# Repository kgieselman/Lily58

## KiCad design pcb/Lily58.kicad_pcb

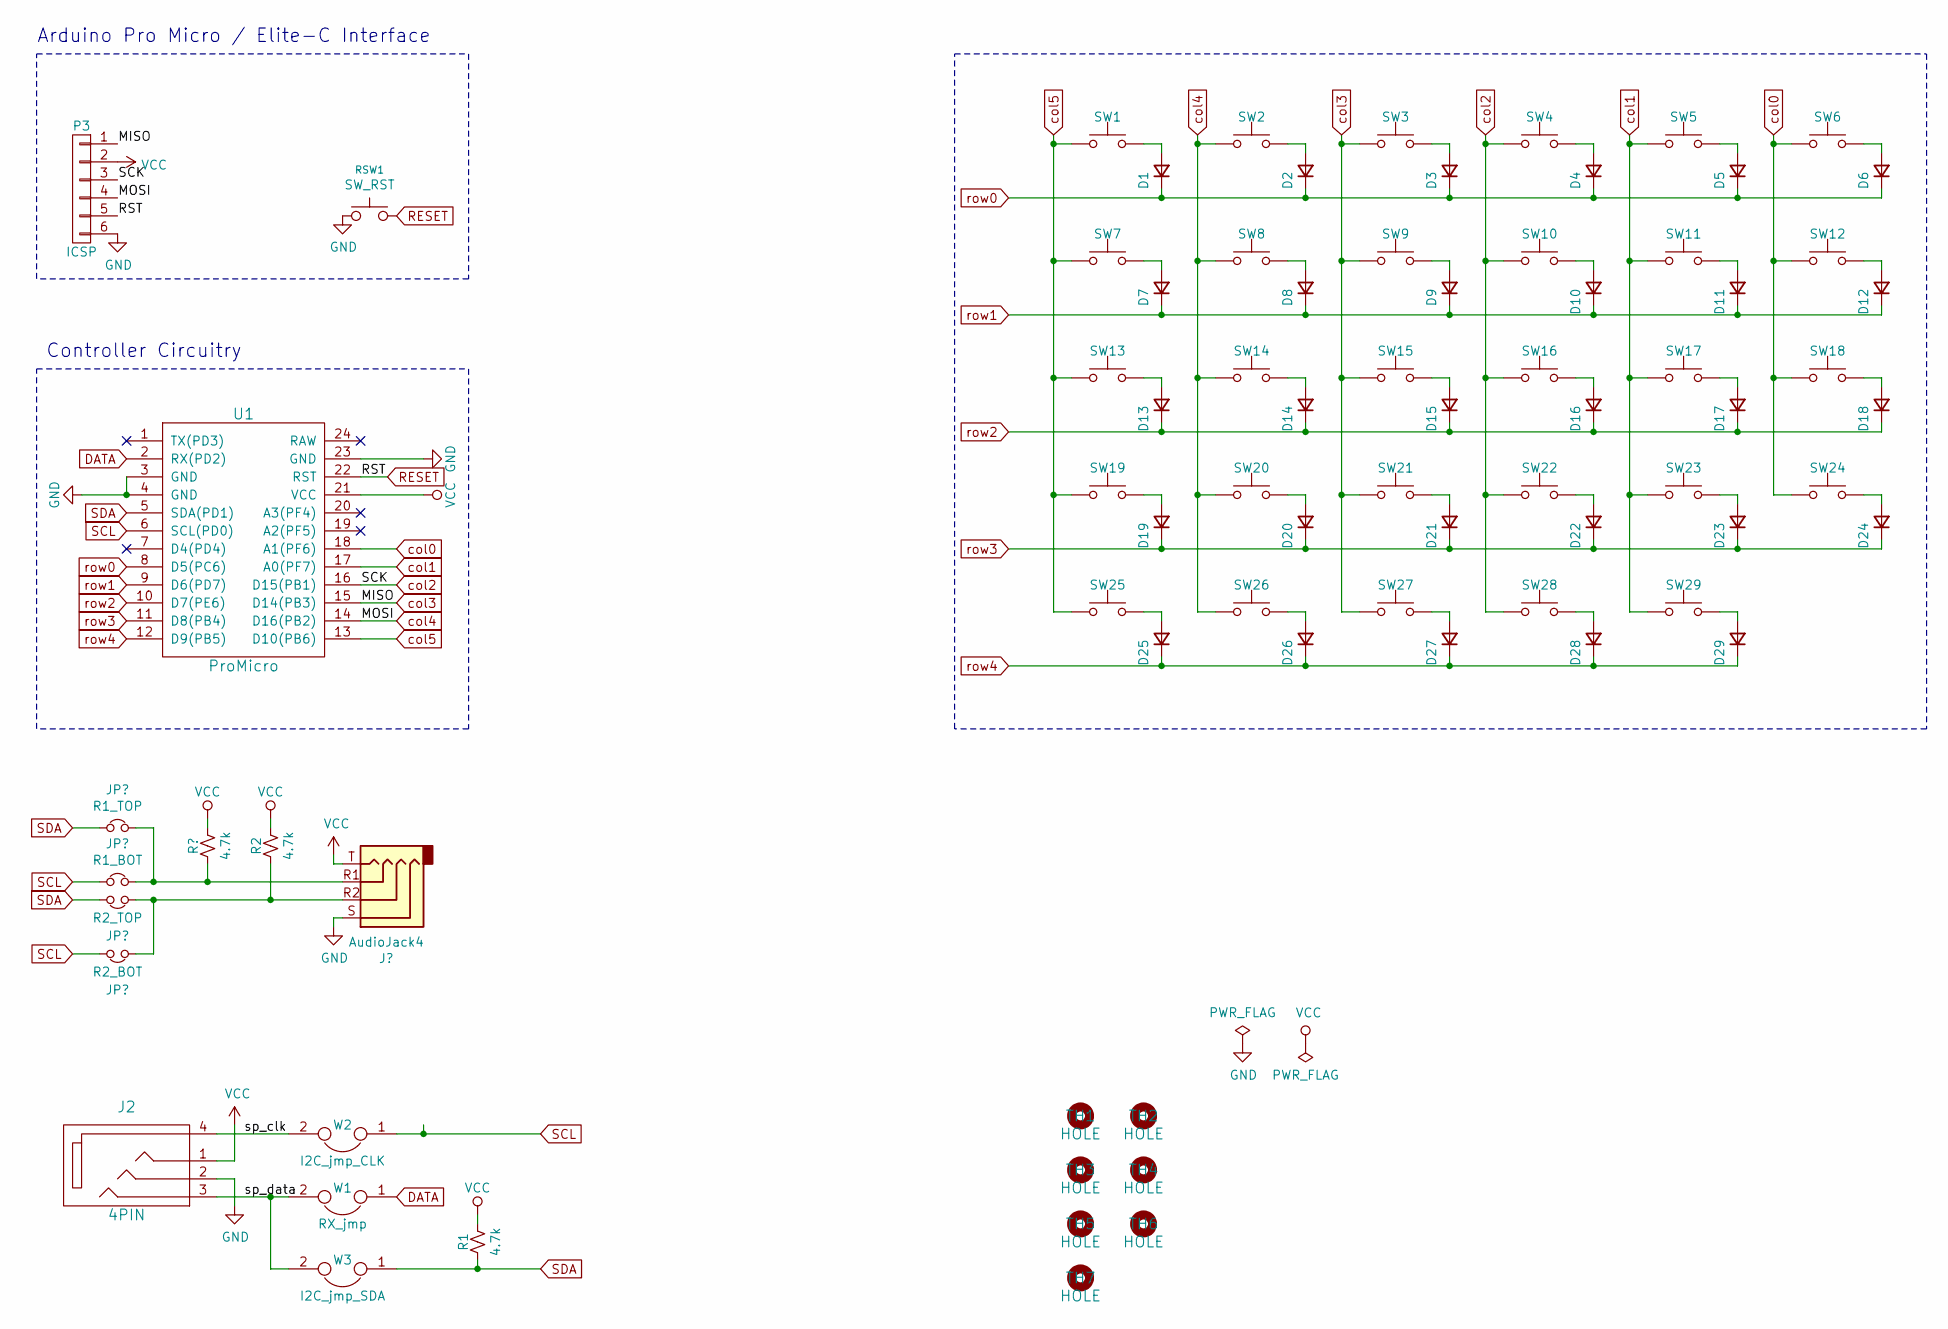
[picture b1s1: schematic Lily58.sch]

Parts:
D1, D2, D3, D4, D5, D6, D7, D8, D9, D10, D11, D12, D13, D14, D15, D16, D17, D18, D19, D20, D21, D22, D23, D24, D25, D26, D27, D28, D29: D; D_SOD-123
J2: 4PIN; MJ-4PP-9
P3: ICSP
R1, R2: 4.7k; R_0603
RSW1: SW_RST; TACT_SWITCH_TVBP06
SW1, SW2, SW3, SW4, SW5, SW6, SW7, SW8, SW9, SW10, SW11, SW12, SW13, SW14, SW15, SW16, SW17, SW18, SW19, SW20, SW21, SW22, SW23, SW24, SW25, SW27, SW28, SW29: SW_PUSH; MX_1U
SW26: SW_PUSH; MX_PG1350-Under_FLIP_HOLES_27mm
TH1, TH2: HOLE; HOLE_M2
TH3, TH4, TH5, TH6, TH7: HOLE; HOLE_M2_TH
U1: ProMicro; ProMicro_rev
W1: RX_jmp; jumper_data
W2: I2C_jmp_CLK; jumper_data
W3: I2C_jmp_SDA; jumper_data

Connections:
/sp_clk: J2.4, W2.2
/sp_data: J2.3, W1.2, W3.2
DATA: U1.2 (RX(PD2)), W1.1
GND: J2.2, P3.6, RSW1.1, U1.3 (GND), U1.4 (GND), U1.23 (GND)
unnamed: D1.2 (A), SW1.2
unnamed: D2.2 (A), SW2.2
unnamed: D3.2 (A), SW3.2
unnamed: D4.2 (A), SW4.2
unnamed: D5.2 (A), SW5.2
unnamed: D6.2 (A), SW6.2
unnamed: D7.2 (A), SW7.2
unnamed: D8.2 (A), SW8.2
unnamed: D9.2 (A), SW9.2
unnamed: D10.2 (A), SW10.2
unnamed: D11.2 (A), SW11.2
unnamed: D12.2 (A), SW12.2
unnamed: D13.2 (A), SW13.2
unnamed: D14.2 (A), SW14.2
unnamed: D15.2 (A), SW15.2
unnamed: D16.2 (A), SW16.2
unnamed: D17.2 (A), SW17.2
unnamed: D18.2 (A), SW18.2
unnamed: D19.2 (A), SW19.2
unnamed: D20.2 (A), SW20.2
unnamed: D21.2 (A), SW21.2
unnamed: D22.2 (A), SW22.2
unnamed: D23.2 (A), SW23.2
unnamed: D24.2 (A), SW24.2
unnamed: D25.2 (A), SW25.2
unnamed: D26.2 (A), SW26.2
unnamed: D27.2 (A), SW27.2
unnamed: D28.2 (A), SW28.2
unnamed: D29.2 (A), SW29.2
RESET: P3.5, RSW1.2, U1.22 (RST)
SCL: R2.2, U1.6 (SCL(PD0)), W2.1
SDA: R1.2, U1.5 (SDA(PD1)), W3.1
VCC: J2.1, P3.2, R1.1, R2.1, U1.21 (VCC)
col0: SW6.1, SW12.1, SW18.1, SW24.1, U1.18 (A1(PF6))
col1: SW5.1, SW11.1, SW17.1, SW23.1, SW29.1, U1.17 (A0(PF7))
col2: P3.3, SW4.1, SW10.1, SW16.1, SW22.1, SW28.1, U1.16 (D15(PB1))
col3: P3.1, SW3.1, SW9.1, SW15.1, SW21.1, SW27.1, U1.15 (D14(PB3))
col4: P3.4, SW2.1, SW8.1, SW14.1, SW20.1, SW26.1, U1.14 (D16(PB2))
col5: SW1.1, SW7.1, SW13.1, SW19.1, SW25.1, U1.13 (D10(PB6))
row0: D1.1 (K), D2.1 (K), D3.1 (K), D4.1 (K), D5.1 (K), D6.1 (K), U1.8 (D5(PC6))
row1: D7.1 (K), D8.1 (K), D9.1 (K), D10.1 (K), D11.1 (K), D12.1 (K), U1.9 (D6(PD7))
row2: D13.1 (K), D14.1 (K), D15.1 (K), D16.1 (K), D17.1 (K), D18.1 (K), U1.10 (D7(PE6))
row3: D19.1 (K), D20.1 (K), D21.1 (K), D22.1 (K), D23.1 (K), D24.1 (K), U1.11 (D8(PB4))
row4: D25.1 (K), D26.1 (K), D27.1 (K), D28.1 (K), D29.1 (K), U1.12 (D9(PB5))

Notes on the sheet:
Arduino Pro Micro / Elite-C Interface
Controller Circuitry

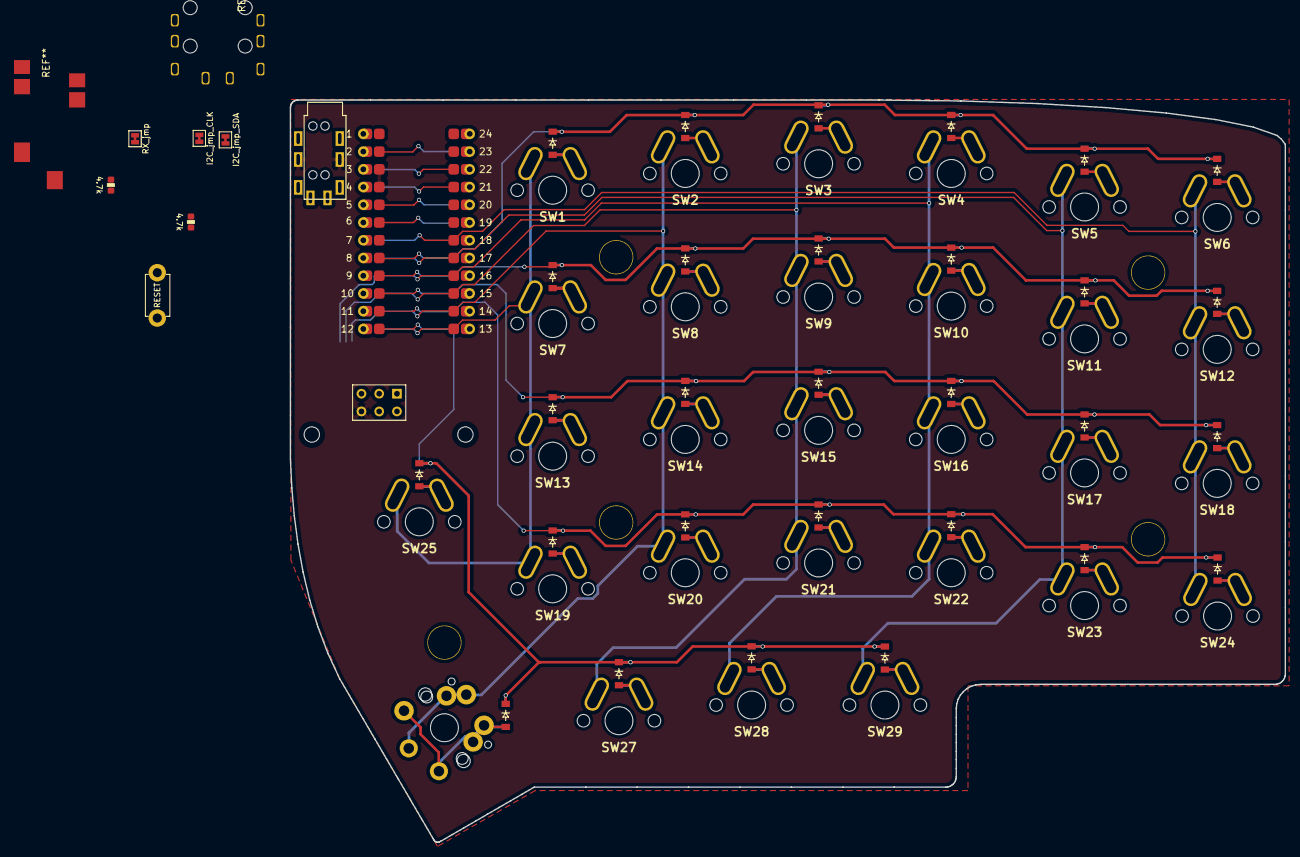
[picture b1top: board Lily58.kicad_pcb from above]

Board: 2 copper layers, 142.5 x 106.3 mm, 74 parts (0 on the bottom side), 48 nets.

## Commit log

2020-09-01 Creating new version with lite as a foundation
2020-09-01 Updated to use my lib (mostly)
2020-09-02 Updated layout to use more comps
    Need to do ATMEGA32U4 circuitry still
2020-09-02 Updated ATMEGA32U4 schematic
2020-09-15 Start of update to use my library and re-route
2020-09-17 Update comps
